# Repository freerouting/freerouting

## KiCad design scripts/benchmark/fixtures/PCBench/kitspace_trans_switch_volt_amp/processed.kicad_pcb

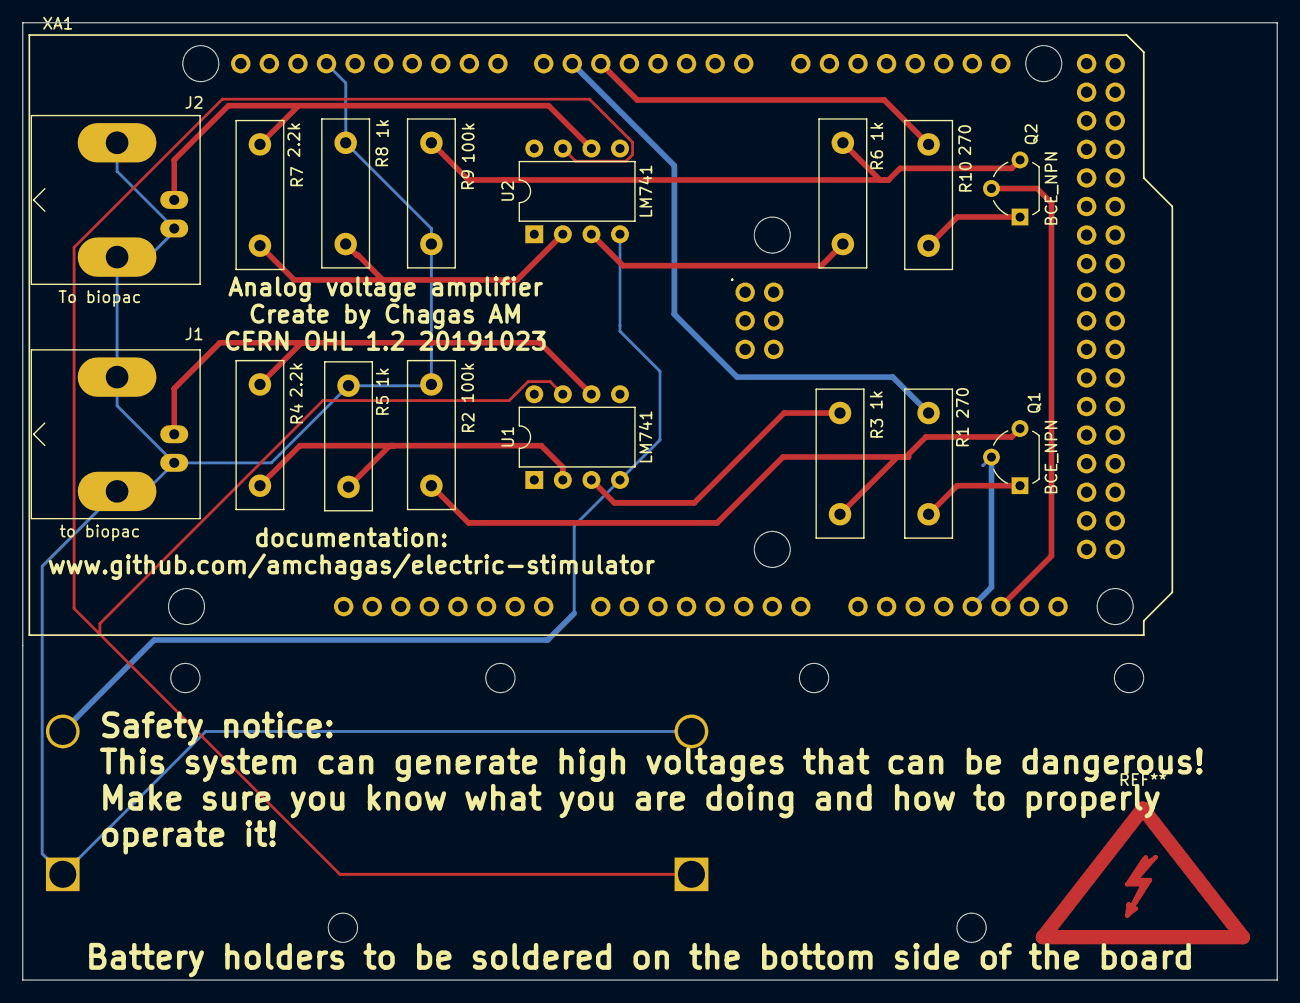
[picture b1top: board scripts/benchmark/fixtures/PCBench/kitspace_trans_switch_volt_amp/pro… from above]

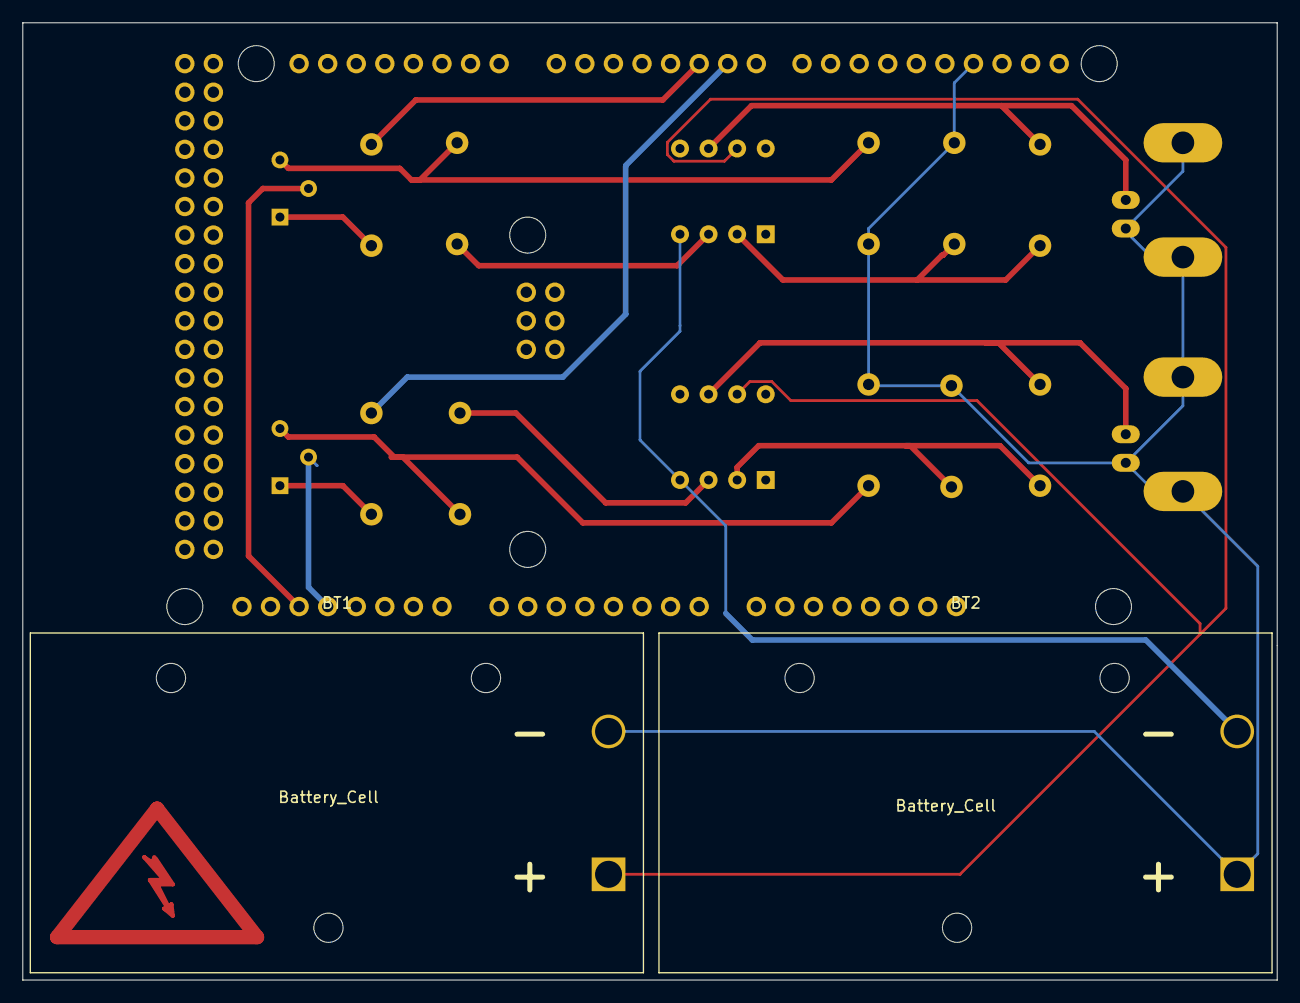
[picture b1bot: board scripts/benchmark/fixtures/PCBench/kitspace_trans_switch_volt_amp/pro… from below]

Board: 2 copper layers, 111.5 x 85.1 mm, 19 parts (2 on the bottom side), 17 nets.

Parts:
BT1, BT2: Battery_Cell; BatteryHolder_Eagle_12BH611-GR
J1: to biopac; BNC_Amphenol_B6252HB-NPP3G-50_Horizontal
J2: To biopac; BNC_Amphenol_B6252HB-NPP3G-50_Horizontal
Q1, Q2: BCE_NPN; TO-92L_Wide
R1, R10: 270; R_Box_L13.0mm_W4.0mm_P9.00mm
R2, R9: 100k; R_Box_L13.0mm_W4.0mm_P9.00mm
R3, R5, R6, R8: 1k; R_Box_L13.0mm_W4.0mm_P9.00mm
R4, R7: 2.2k; R_Box_L13.0mm_W4.0mm_P9.00mm
U1, U2: LM741; DIP-8_W7.62mm
XA1: Arduino_Due_Shield

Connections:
GND: BT1.2, BT2.1, J1.2, J2.2, R2.2, R5.1, R8.1, R9.2, XA1.GND1
unnamed: BT1.1, U1.7, U2.7
unnamed: BT2.2, U1.4, U2.4
unnamed: J1.1, R4.2, U1.6
unnamed: J2.1, R7.2, U2.6
unnamed: Q1.1, R1.1
unnamed: Q1.2, XA1.DAC0
unnamed: Q1.3, R2.1, R3.1
unnamed: Q2.1, R10.1
unnamed: Q2.2, XA1.DAC1
unnamed: Q2.3, R6.1, R9.1
unnamed: R1.2, XA1.D6
unnamed: R3.2, U1.3
unnamed: R4.1, R5.2, U1.2
unnamed: R6.2, U2.3
unnamed: R7.1, R8.2, U2.2
unnamed: R10.2, XA1.D5

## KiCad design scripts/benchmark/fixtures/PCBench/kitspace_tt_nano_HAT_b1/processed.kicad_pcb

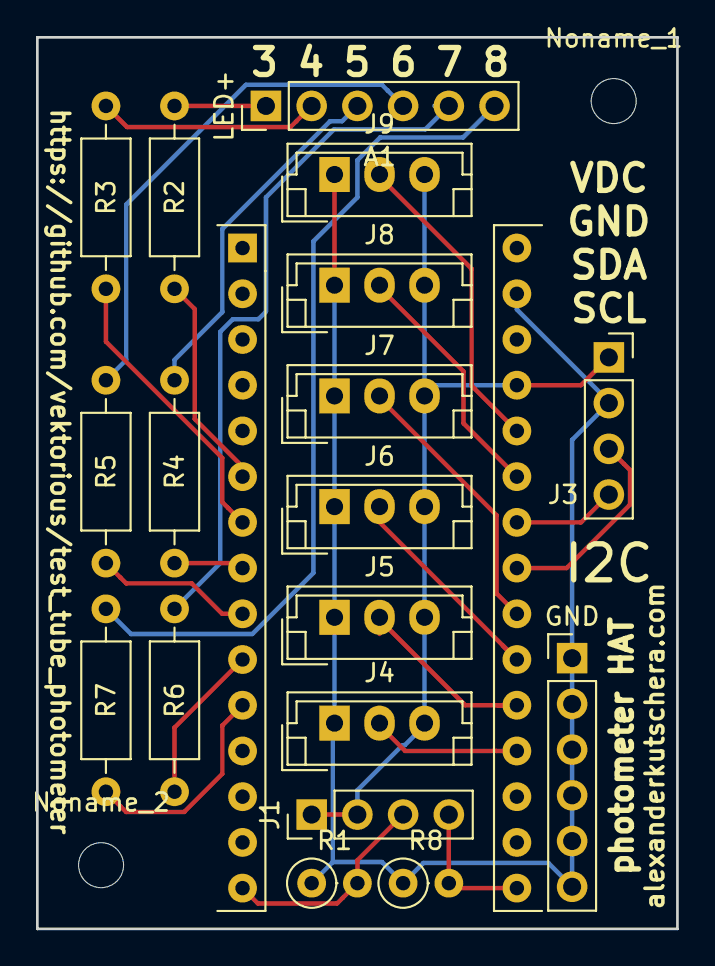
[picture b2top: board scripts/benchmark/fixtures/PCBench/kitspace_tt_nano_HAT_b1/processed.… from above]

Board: 2 copper layers, 35.6 x 49.5 mm, 21 parts (0 on the bottom side), 24 nets.

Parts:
A1: Arduino_Nano_v3.x; Arduino_Nano2
GND: Conn_01x06_Male; PinHeader_1x06_P2.54mm_Vertical
J1: Conn_01x04_Male; PinHeader_1x04_P2.54mm_Vertical
J3: Conn_01x04_Female; PinSocket_1x04_P2.54mm_Vertical
J4, J5, J6, J7, J8, J9: Conn_01x03_Male; JST_EH_B03B-EH-A_1x03_P2.50mm_Vertical
LED+: Conn_01x06_Male; PinHeader_1x06_P2.54mm_Vertical
Noname_1, Noname_2: MountingHole_2.5mm
R1, R8: R; R_Axial_DIN0207_L6.3mm_D2.5mm_P2.54mm_Vertical
R2, R3, R4, R5, R6, R7: R; R_Axial_DIN0207_L6.3mm_D2.5mm_P10.16mm_Horizontal

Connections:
unnamed: A1.6, R2.1
unnamed: A1.7, R3.1
unnamed: A1.8, R4.1
unnamed: A1.9, R5.1
unnamed: A1.10, R6.1
unnamed: A1.11, R7.1
unnamed: A1.15, J1.3, R1.2
unnamed: A1.16, J1.4, R8.2
unnamed: A1.19, J4.2
unnamed: A1.20, J5.2
unnamed: A1.21, J6.2
unnamed: A1.22, J7.2
unnamed: A1.23, J3.3
unnamed: A1.24, J3.4
unnamed: A1.25, J8.2
unnamed: A1.26, J9.2
unnamed: A1.27, J1.1, J1.2, J3.1, J4.3, J5.3, J6.3, J7.3, J8.3, J9.3
unnamed: A1.29, GND.1, GND.2, GND.3, GND.4, GND.5, GND.6, J3.2, J4.1, J5.1, J6.1, J7.1, J8.1, J9.1, R1.1, R8.1
unnamed: LED+.1, R2.2
unnamed: LED+.2, R3.2
unnamed: LED+.3, R4.2
unnamed: LED+.4, R5.2
unnamed: LED+.5, R6.2
unnamed: LED+.6, R7.2

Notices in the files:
scripts/benchmark/fixtures/PCBench/kitspace_trans_switch_volt_amp/processed.kicad_pcb:
CERN OHL 1.2 20191023
